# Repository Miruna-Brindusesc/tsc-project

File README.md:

# Proiect InkTime: Smartwatch nRF52840

## 1\. Diagrama Bloc

Diagrama de mai jos ilustreaza interconexiunile dintre unitatea centrala (MCU) si perifericele sistemului.

## 2\. Descriere Hardware

Ceasul este construit in jurul lui **nRF52840**, ales special pentru ca e foarte eficient si are Bluetooth inclus. Ideea de baza: consumam curent doar cand e absolut necesar.

### 2.1. Creierul (MCU)
* **nRF52840:** Un cip puternic care stie si Bluetooth 5.0 si USB. Are doua cristale de cuart pentru precizie maxima la masurarea timpului.
* **Antena:** Semnalul pleaca spre o antena ceramica. Ca sa avem semnal bun, am decupat planul de cupru de sub ea (zona de "keep-out").

### 2.2. Power & Battery
* **incarcare (BQ25180):** Se ocupa de alimentarea bateriei LiPo prin USB-C. il controlam prin **I2C** ca sa stim cand s-a incarcat.
* **Fuel Gauge (MAX17048):** E senzorul. Ne spune exact cat % mai are bateria, cu o eroare de sub 1%.
* **Regulator (RT6160A):** Transforma tensiunea variabila a bateriei intr-un **3.3V stabil** pentru toate componentele.
* **Protectie ESD:** Langa mufa USB-C am pus un cip minuscul (USBLC6) care atenueaza socurile de electricitate statica sa nu prajim placa.

### 2.3. Ecran si Vibratii
* **E-Paper Display:** Cel mai mare avantaj. Consuma curent **doar cand schimba imaginea**. Daca ceasul sta pe loc, consumul e zero.
* **Driverul de ecran:** Pentru ca ecranul are nevoie de tensiuni mari ca sa miste cerneala electronica, am adaugat un circuit special cu diode si condensatori de 50V.
* **Vibratii (Haptic):** Folosim un driver **DRV2605** care misca motorasul. E mult mai destept decat un simplu tranzistor, oferind vibratii mai fine.

### 2.4. Senzori si Butoane
* **Miscare (BMA423):** Accelerometrul care numara pasii. L-am legat pe **I2C** si are pini de intrerupere (INT) ca sa „trezeasca” ceasul cand ridici mana.
* **Butoane:** Avem 3 butoane cu filtre hardware (rezistente si condensatori) ca sa nu avem probleme cu „apasarile false” (debounce).

## 3\. Asociere pini

| Grupa de pini | Pini folositi | Componenta | Justificarea alegerii / Functia |
| :--- | :--- | :--- | :--- |
| **I2C (SDA/SCL)** | **P0.26 / P0.27** | BQ25180, MAX17048, BMA423, DRV2605 | Magistrala comuna; pinii au fost pozitionati departe de zona antenei pentru a evita interferentele RF. |
| **Display (SPI)** | **P0.13, P0.14, P0.19** | E-Paper Connector | Rutare scurta si directa catre conectorul FPC, minimizand lungimea traseelor de mare viteza. |
| **Display Control** | **P0.20, P0.21, P0.23** | E-Paper Connector | Pini GPIO pentru semnalele de DC, Reset si Busy. Pinul Busy actioneaza ca intrerupere (INT). |
| **Power Gate** | **P0.24** | Tranzistor Q1 (Load Switch) | Ofera curent suficient pentru a comuta poarta MOSFET-ului, oprind complet ecranul in standby. |
| **Butoane & Alerte**| **P1.00 - P1.06** | Butoane externe, Alerte IMU / Baterie | Folosirea exclusiva a Portului 1 pentru semnale lente/intreruperi, izolandu-le de magistralele de date si permitand functia de Wake-Up eficient. |
| **Haptic Enable** | **P0.25** | DRV2605 (Motor Haptic) | Pin GPIO folosit pentru pornirea/oprirea cipului haptic. |
| **USB** | **VBUS, D+, D-** | Conector USB-C | Pini hardware dedicati ai PHY-ului intern nRF52840 pentru comunicatie nativa. |
| **Programare (SWD)** | **SWDIO, SWDCLK, SWO**| Conector Tag-Connect | Pini dedicati din fabrica pentru interfata Serial Wire Debug. |
| **Ceas (Oscilator)** | **P0.00, P0.01** | Cristal 32.768 kHz | Pini hardware dedicati (LFXO) pentru conectarea cristalului extern necesar functiilor de Low-Power Sleep. |

## 4\. BOM
| Qty | Componenta | Designator | Cod JLC / Sursa | Datasheet / Link |
| :--- | :--- | :--- | :--- | :--- |
| 1 | **nRF52840 (MCU)** | U1 | [C190740](https://www.google.com/search?q=https://jlcpcb.com/partdetail/NordicSemicon-NRF52840_QIAA/C190740) | [Datasheet](https://www.google.com/search?q=https://infocenter.nordicsemi.com/pdf/nRF52840_PS_v1.1.pdf) |
| 1 | **BMA423 (IMU)** | IC3 | [C262-BMA423](https://jlcpcb.com/parts) | [Datasheet](https://www.google.com/search?q=https://www.bosch-sensortec.com/media/boschsensortec/downloads/datasheets/bst-bma423-ds000.pdf) |
| 1 | **BQ25180 (Charger)** | IC1 | [C595-BQ25180](https://jlcpcb.com/parts) | [Datasheet](https://www.ti.com/lit/ds/symlink/bq25180.pdf) |
| 1 | **MAX17048 (Fuel Gauge)** | U3 | [C329239](https://jlcpcb.com/parts) | [Datasheet](https://www.google.com/search?q=https://datasheets.maximintegrated.com/en/ds/MAX17048-MAX17049.pdf) |
| 1 | **RT6160A (DC/DC)** | IC9 | [C835-RT6160](https://jlcpcb.com/parts) | [Datasheet](https://www.google.com/search?q=https://www.richtek.com/assets/product_pdf/RT6160A/DS6160A-02.pdf) |
| 1 | **DRV2605 (Haptic)** | IC4 | [C519213](https://jlcpcb.com/parts) | [Datasheet](https://www.ti.com/lit/ds/symlink/drv2605.pdf) |
| 1 | **E-Paper Conn (24 pin)**| J1 | [C262444](https://jlcpcb.com/parts) | [Link Molex](https://www.molex.com/en-us/products/part-detail/5034802400) |
| 1 | **USB-C (16 pin)** | J4 | [C719112](https://jlcpcb.com/parts) | [Datasheet](https://www.google.com/search?q=https://datasheet.lcsc.com/lcsc/2110271930_KINGHELM-KH-TYPE-C-16P_C2835407.pdf) |
| 1 | **Antena 2.45GHz** | ANT1 | [C96280](https://jlcpcb.com/parts) | [Datasheet](https://www.johansontechnology.com/datasheets/2450AT18B100.pdf) |
| 3 | **Butoane EVP-AKE31A** | SW1-SW3 | [C519154](https://jlcpcb.com/parts) | [Datasheet](https://www.google.com/search?q=https://industrial.panasonic.com/cdbs/www-data/pdf/SMG0000/SMG0000C191.pdf) |
| 1 | **USBLC6-2 (ESD)** | D3 | [C75248](https://jlcpcb.com/parts) | [Datasheet](https://www.st.com/resource/en/datasheet/usblc6-2.pdf) |
| 1 | **DMG2305UX (P-FET)** | Q1 | [C14388](https://jlcpcb.com/parts) | [Datasheet](https://www.diodes.com/assets/Datasheets/DMG2305UX.pdf) |

## 5\. Decizii

### 5.1. Decizii de amplasare a componentelor

Privind asezarea componentelor pe PCB, au fost luate urmatoarele decizii strategice pentru a optimiza spatiul si performanta:

* **Planuri de Masa (GND Pours) pe ambele straturi:** Am implementat poligoane de GND atat pe stratul Top, cat si pe Bottom, cusute cu via-uri (vias). Aceasta decizie are trei roluri majore:
    1.  **Ecranare EMI:** Reduce zgomotul electric dintre traseele de semnal.
    2.  **Disipare Termica:** Ajuta la disiparea caldurii generate de convertorul DC/DC si de circuitul de incarcare a bateriei.
    3.  **Referinta RF:** Ofera un plan de referinta solid pentru performanta optima a antenei Bluetooth.
* **Amplasarea Antenei (RF Keep-out Zone):** Antena ceramica de 2.4GHz a fost plasata pe extrema dreapta a placii.

* **Gruparea Circuitului E-Paper:** Componentele voluminoase si zgomotoase aferente display-ului (bobina, diodele si condensatorii pentru tensiunile de VGH/VGL) sunt grupate extrem de compact in stanga, imediat langa conectorul FPC. Aceasta mentine traseele de inalta tensiune scurte si departe de liniile sensibile ale MCU-ului.

### 5.2. Erori

#### Erori ERC (Electrical Rule Check)
* **Conflicte de alimentare (U1, U3):** Softul da eroare pentru ca mai multi pini `VDD` se leaga la aceeasi retea (`3V3` sau `VBAT`). Conexiunile sunt 100% corecte conform datasheet-urilor; eroarea apare doar pentru ca softul e prea strict cu regulile de „Power Source”.
* **Pinii de decuplare (DEC1, DEC4):** Aceeasi poveste la nRF52840. Pinii sunt legati corect la condensatori externi exact cum cere producatorul, dar softul nu ii recunoaste ca noduri clasice de alimentare.
* **Componente fara valoare (SJ1):** Jumper-ul de pe placa (SJ1) este doar un bridge fizic (Solder Jumper) folosit pentru configurare. Fiind un simplu contact de fludor, e normal sa nu aiba o valoare numerica (gen 10kΩ).
* **Erorile de tip "Only one pin on net"** (pe SDA/SCL) arata ca acele trasee sunt lasate libere.

#### Erori DRC (Design Rule Check)
Deoarece acest PCB este un *Proof of Concept* software si nu merge fizic la o fabrica, am prioritizat logica si functionalitatea in fata unui raport DRC complet verde:
* **Erori de margine (Board Outline Clearance):** Sunt 8 erori aici.Conectorul USB-C si butoanele sunt apropiate de marginile placutei, ceea ce declanseaza automat eroarea.
* **Suprapuneri pe planul de masa (Polygon Overlap):** Placa foloseste piese minuscule (0201/0402) si este foarte aglomerata. Am fortat poligonul de masa (GND) sa acopere cat mai mult spatiu pentru o buna disipare termica. Asta a generat niste erori de "clearance" la pad-uri, dar am preferat un plan de masa solid in detrimentul unui DRC perfect.

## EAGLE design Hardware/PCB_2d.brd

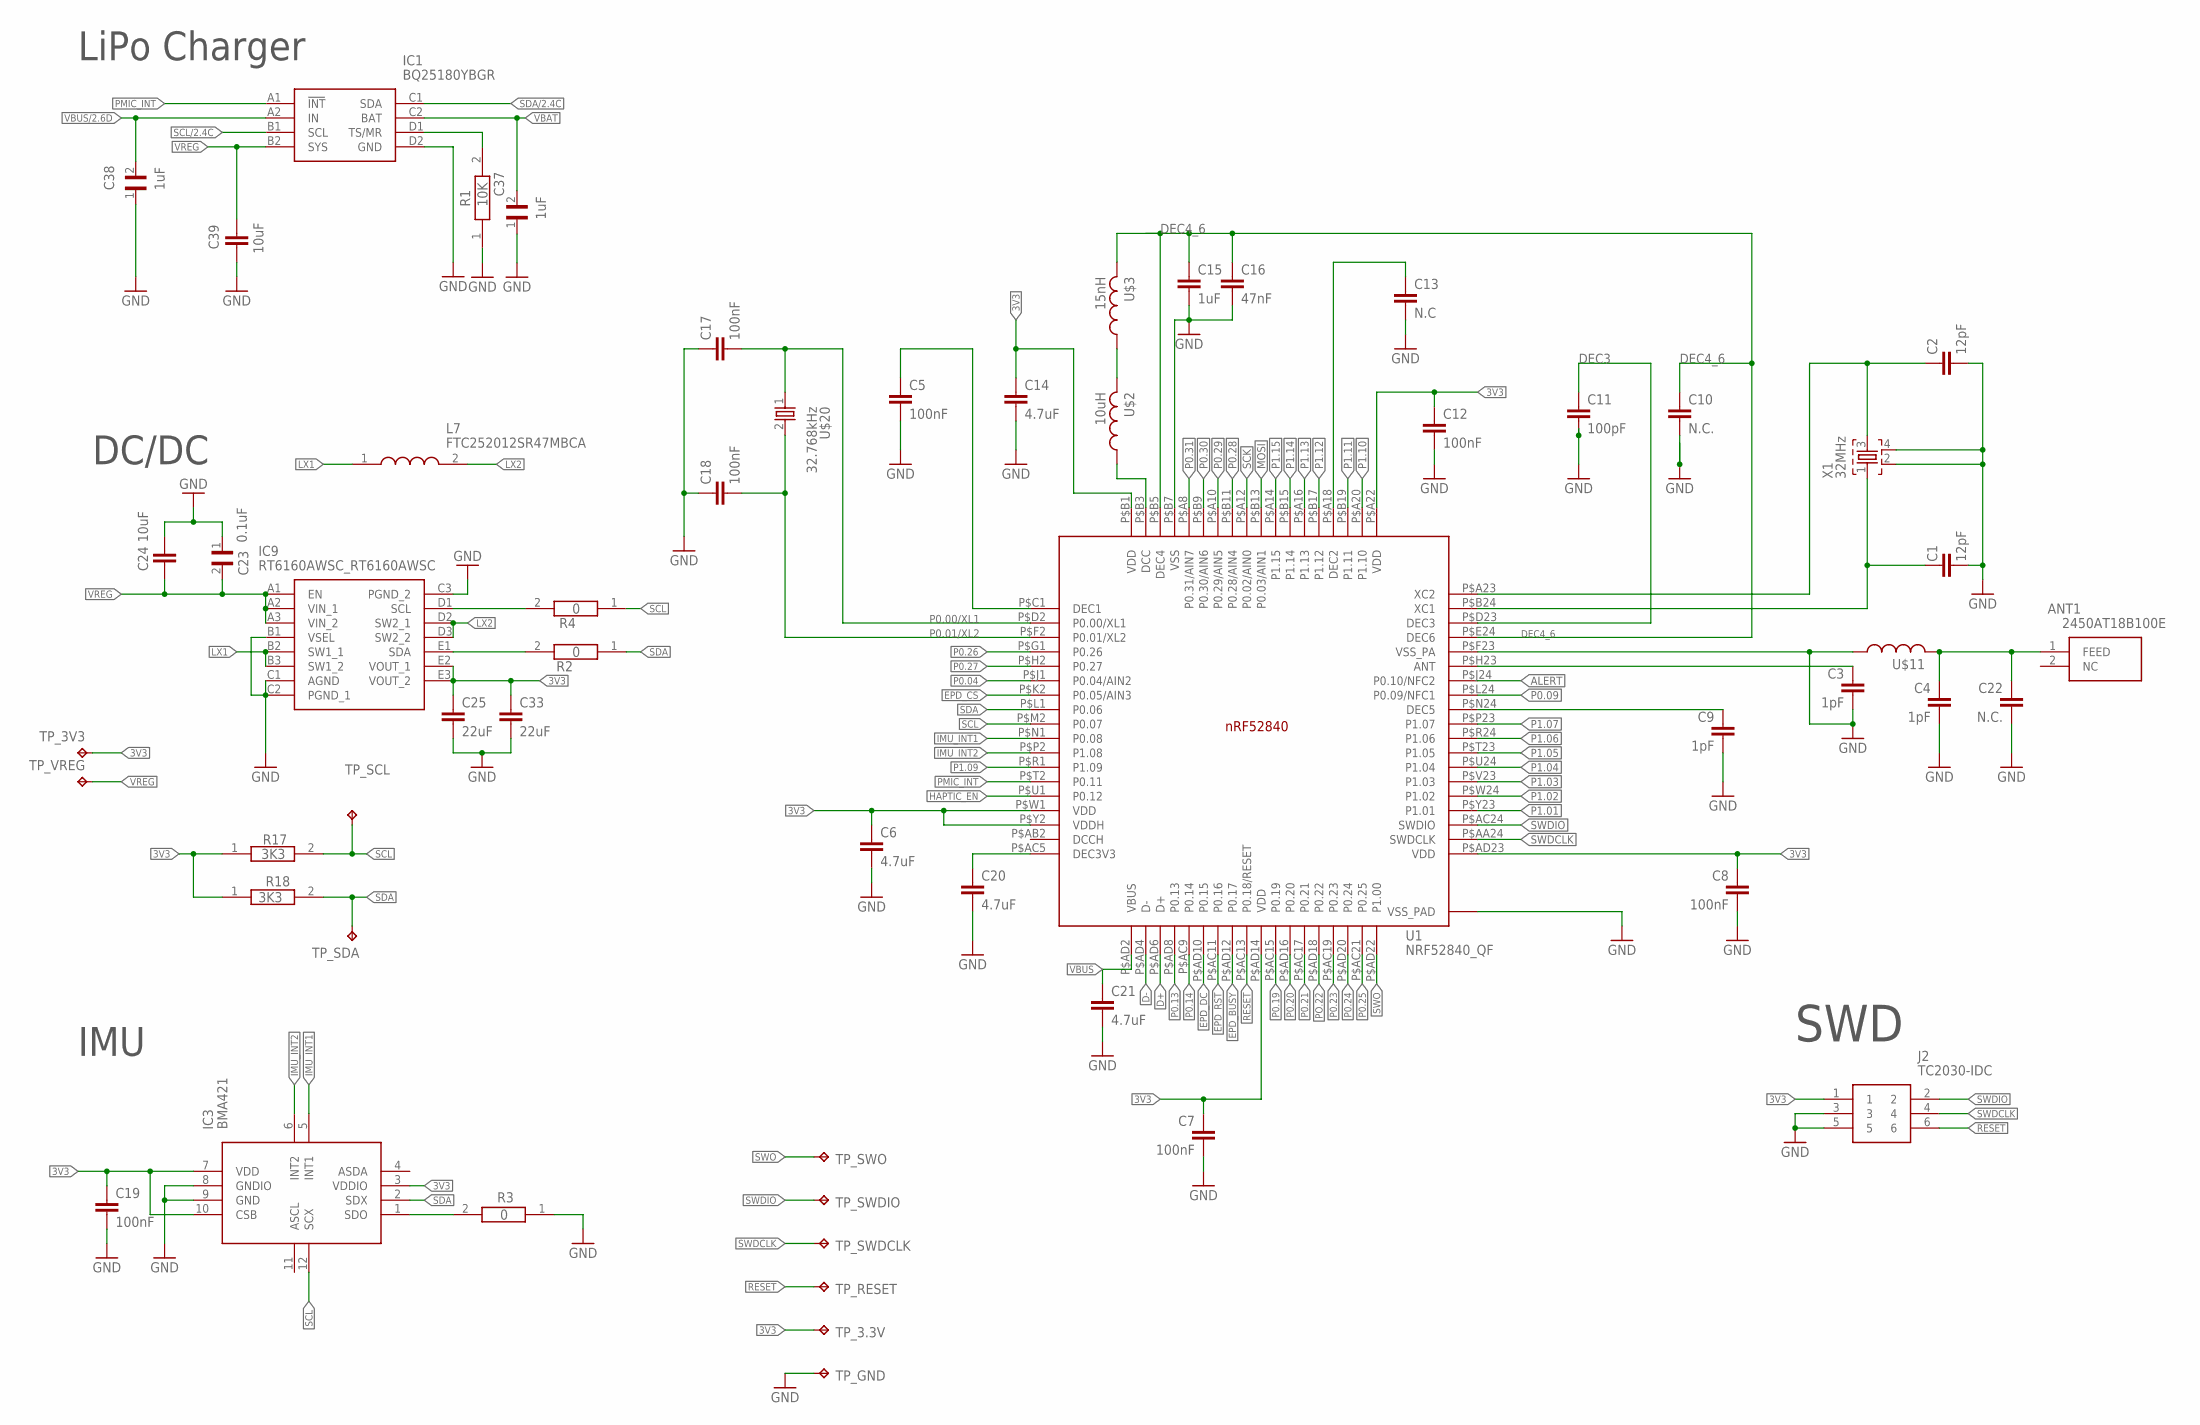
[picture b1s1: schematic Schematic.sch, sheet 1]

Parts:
ANT1: 2450AT18B100E; 2450AT18B100E_ANTC3216X140N
C1, C2: 12pF; NORDIC_NRF_3_RESC0201_L
C3, C4, C9: 1pF; NORDIC_NRF_3_RESC0201_L
C5, C7, C8, C12, C17, C18, C19: 100nF; NORDIC_NRF_3_RESC0201_L
C6, C14, C20, C21: 4.7uF; PERFECT_0402_0402
C10, C22: N.C.; NORDIC_NRF_3_RESC0201_L
C11: 100pF; NORDIC_NRF_3_RESC0201_L
C13: N.C; NORDIC_NRF_3_RESC0201_L
C15: 1uF; PERFECT_0402_0402
C16: 47nF; NORDIC_NRF_3_RESC0201_L
C23: 0.1uF; GRM011R60J152KE01L_2_CAPC0201X13N
C24, C39: 10uF; PERFECT_0402_0402
C25, C33: 22uF; PERFECT_0402_0402
C37, C38: 1uF; GRM011R60J152KE01L_1_0201
IC1: BQ25180YBGR; BQ25180YBGR_BGA8C40P2X4_100X155X50
IC3: BMA421; BMA423_BMA423
IC9: RT6160AWSC_RT6160AWSC; RT6160AWSC_BGA15C40P3X5_140X230X60
J2: TC2030-IDC; TC2030-IDC_TC2030IDC
L7: FTC252012SR47MBCA; MLP2016SR47MT0S1_INDC2016X100N
R1: 10K; CPF0201D7K68C1_0201
R2, R3, R4: 0; CPF0201D7K68C1_0201
R17, R18: 3K3; CPF0201D7K68C1_0201
TP_3.3V, TP_3V3: HECTOR_WATCH_1_TPTP20R; HECTOR_WATCH_1_TP20R
TP_GND: HECTOR_WATCH_1_TPTP20R; HECTOR_WATCH_1_TP20R
TP_RESET: HECTOR_WATCH_1_TPTP20R; HECTOR_WATCH_1_TP20R
TP_SCL: HECTOR_WATCH_1_TPTP20R; HECTOR_WATCH_1_TP20R
TP_SDA: HECTOR_WATCH_1_TPTP20R; HECTOR_WATCH_1_TP20R
TP_SWDCLK: HECTOR_WATCH_1_TPTP20R; HECTOR_WATCH_1_TP20R
TP_SWDIO: HECTOR_WATCH_1_TPTP20R; HECTOR_WATCH_1_TP20R
TP_SWO: HECTOR_WATCH_1_TPTP20R; HECTOR_WATCH_1_TP20R
TP_VREG: HECTOR_WATCH_1_TPTP20R; HECTOR_WATCH_1_TP20R
U1: NRF52840_QF; NORDIC_NRF_4_AQFN50P700X700X85_HS-74N
U$2: 10uH; NORDIC_NRF_2_RESC0402_L
U$3: 15nH; NORDIC_NRF_2_RESC0402_L
U$11: NORDIC_NRF_2_INDUCTOR_0402_L; NORDIC_NRF_2_RESC0402_L
U$20: 32.768kHz; NORDIC_NRF_1_XTAL_3215_N
X1: 32MHz; NORDIC_NRF_BT-XTAL_2016_N

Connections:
3V3: C6.1, C7.1, C8.1, C12.1, C14.1, C19.1, C25.1, C33.1, IC3.3 (VDDIO), IC3.7 (VDD), IC3.10 (CSB), IC9.E2 (VOUT_1), IC9.E3 (VOUT_2), J2.1, R17.1, R18.1, TP_3.3V.TP, TP_3V3.TP, U1.P$A22 (VDD), U1.P$AD14 (VDD), U1.P$AD23 (VDD), U1.P$B1 (VDD), U1.P$W1 (VDD), U1.P$Y2 (VDDH); also elsewhere on the board
ALERT: U1.P$J24 (P0.10/NFC2); also elsewhere on the board
D+: U1.P$AD6 (D+); also elsewhere on the board
D-: U1.P$AD4 (D-); also elsewhere on the board
DEC3: C11.1, U1.P$D23 (DEC3)
DEC4_6: C10.1, C15.1, C16.1, U1.P$B5 (DEC4), U1.P$E24 (DEC6), U$3.2
EPD_BUSY: U1.P$AD12 (P0.17); also elsewhere on the board
EPD_CS: U1.P$K2 (P0.05/AIN3); also elsewhere on the board
EPD_DC: U1.P$AD10 (P0.15); also elsewhere on the board
EPD_RST: U1.P$AC11 (P0.16); also elsewhere on the board
GND: C1.2, C2.2, C3.2, C4.2, C5.2, C6.2, C7.2, C8.2, C9.2, C10.2, C11.2, C12.2, C13.2, C14.2, C15.2, C16.2, C17.1, C18.1, C19.2, C20.2, C21.2, C22.2, C23.1, C24.1, C25.2, C33.2, C37.1, C38.1, C39.2, IC1.D2 (GND), IC3.8 (GNDIO), IC3.9 (GND), IC9.B1 (VSEL), IC9.C1 (AGND), IC9.C2 (PGND_1), IC9.C3 (PGND_2), J2.3, J2.5, R1.1, R3.1, TP_GND.TP, U1.P$74 (VSS_PAD), U1.P$75 (VSS_PAD), U1.P$76 (VSS_PAD), U1.P$77 (VSS_PAD), U1.P$78 (VSS_PAD), U1.P$79 (VSS_PAD), U1.P$80 (VSS_PAD), U1.P$81 (VSS_PAD), U1.P$82 (VSS_PAD), U1.P$83 (VSS_PAD), U1.P$84 (VSS_PAD), U1.P$85 (VSS_PAD), U1.P$86 (VSS_PAD), U1.P$87 (VSS_PAD), U1.P$88 (VSS_PAD), U1.P$89 (VSS_PAD), U1.P$90 (VSS_PAD), U1.P$B7 (VSS), U1.P$F23 (VSS_PA), U$11.1, X1.2, X1.4; also elsewhere on the board
HAPTIC_EN: U1.P$U1 (P0.12); also elsewhere on the board
IMU_INT1: IC3.5 (INT1), U1.P$N1 (P0.08)
IMU_INT2: IC3.6 (INT2), U1.P$P2 (P1.08)
LX1: IC9.B2 (SW1_1), IC9.B3 (SW1_2), L7.1
LX2: IC9.D2 (SW2_1), IC9.D3 (SW2_2), L7.2
MOSI: U1.P$B13 (P0.03/AIN1); also elsewhere on the board
unnamed: U1.P$B3 (DCC), U$2.1
unnamed: U$2.2, U$3.1
unnamed: C13.1, U1.P$A18 (DEC2)
unnamed: IC9.E1 (SDA), R2.2
unnamed: IC9.D1 (SCL), R4.2
unnamed: C1.1, U1.P$B24 (XC1), X1.1
unnamed: C2.1, U1.P$A23 (XC2), X1.3
unnamed: ANT1.1 (FEED), C4.1, C22.1, U$11.2
unnamed: C3.1, U1.P$H23 (ANT)
unnamed: C9.1, U1.P$N24 (DEC5)
unnamed: C5.1, U1.P$C1 (DEC1)
unnamed: C20.1, U1.P$AC5 (DEC3V3)
unnamed: IC1.D1 (TS/MR), R1.2
unnamed: IC3.1 (SDO), R3.2
P0.00/XL1: C17.2, U1.P$D2 (P0.00/XL1), U$20.1
P0.01/XL2: C18.2, U1.P$F2 (P0.01/XL2), U$20.2
P0.04: U1.P$J1 (P0.04/AIN2)
P0.09: U1.P$L24 (P0.09/NFC1)
P0.13: U1.P$AD8 (P0.13); also elsewhere on the board
P0.14: U1.P$AC9 (P0.14); also elsewhere on the board
P0.19: U1.P$AC15 (P0.19)
P0.20: U1.P$AD16 (P0.20)
P0.21: U1.P$AC17 (P0.21)
P0.23: U1.P$AC19 (P0.23)
P0.24: U1.P$AD20 (P0.24)
P0.25: U1.P$AC21 (P0.25)
P0.26: U1.P$G1 (P0.26)
P0.27: U1.P$H2 (P0.27)
P0.28: U1.P$B11 (P0.28/AIN4)
P0.29: U1.P$A10 (P0.29/AIN5)
P0.30: U1.P$B9 (P0.30/AIN6)
P0.31: U1.P$A8 (P0.31/AIN7)
P1.01: U1.P$Y23 (P1.01); also elsewhere on the board
P1.02: U1.P$W24 (P1.02); also elsewhere on the board
P1.03: U1.P$V23 (P1.03)
P1.04: U1.P$U24 (P1.04)
P1.05: U1.P$T23 (P1.05)
P1.06: U1.P$R24 (P1.06)
P1.07: U1.P$P23 (P1.07)
P1.09: U1.P$R1 (P1.09)
P1.10: U1.P$A20 (P1.10)
P1.11: U1.P$B19 (P1.11)
P1.12: U1.P$B17 (P1.12)
P1.13: U1.P$A16 (P1.13)
P1.14: U1.P$B15 (P1.14)
P1.15: U1.P$A14 (P1.15)
PMIC_INT: IC1.A1 (!INT), U1.P$T2 (P0.11)
PO.22: U1.P$AD18 (P0.22)
RESET: J2.6, TP_RESET.TP, U1.P$AC13 (P0.18/RESET)
SCK: U1.P$A12 (P0.02/AIN0); also elsewhere on the board
SCL: IC3.12 (SCX), R4.1, R17.2, TP_SCL.TP, U1.P$M2 (P0.07); also elsewhere on the board
SCL/2.4C: IC1.B1 (SCL)
SDA: IC3.2 (SDX), R2.1, R18.2, TP_SDA.TP, U1.P$L1 (P0.06); also elsewhere on the board
SDA/2.4C: IC1.C1 (SDA)
SWDCLK: J2.4, TP_SWDCLK.TP, U1.P$AA24 (SWDCLK)
SWDIO: J2.2, TP_SWDIO.TP, U1.P$AC24 (SWDIO)
SWO: TP_SWO.TP, U1.P$AD22 (P1.00)
VBAT: C37.2, IC1.C2 (BAT); also elsewhere on the board
VBUS: C21.1, U1.P$AD2 (VBUS); also elsewhere on the board
VBUS/2.6D: C38.2, IC1.A2 (IN)
VREG: C23.2, C24.2, C39.1, IC1.B2 (SYS), IC9.A1 (EN), IC9.A2 (VIN_1), IC9.A3 (VIN_2), TP_VREG.TP

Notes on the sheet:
DC/DC
LiPo Charger
IMU
SWD

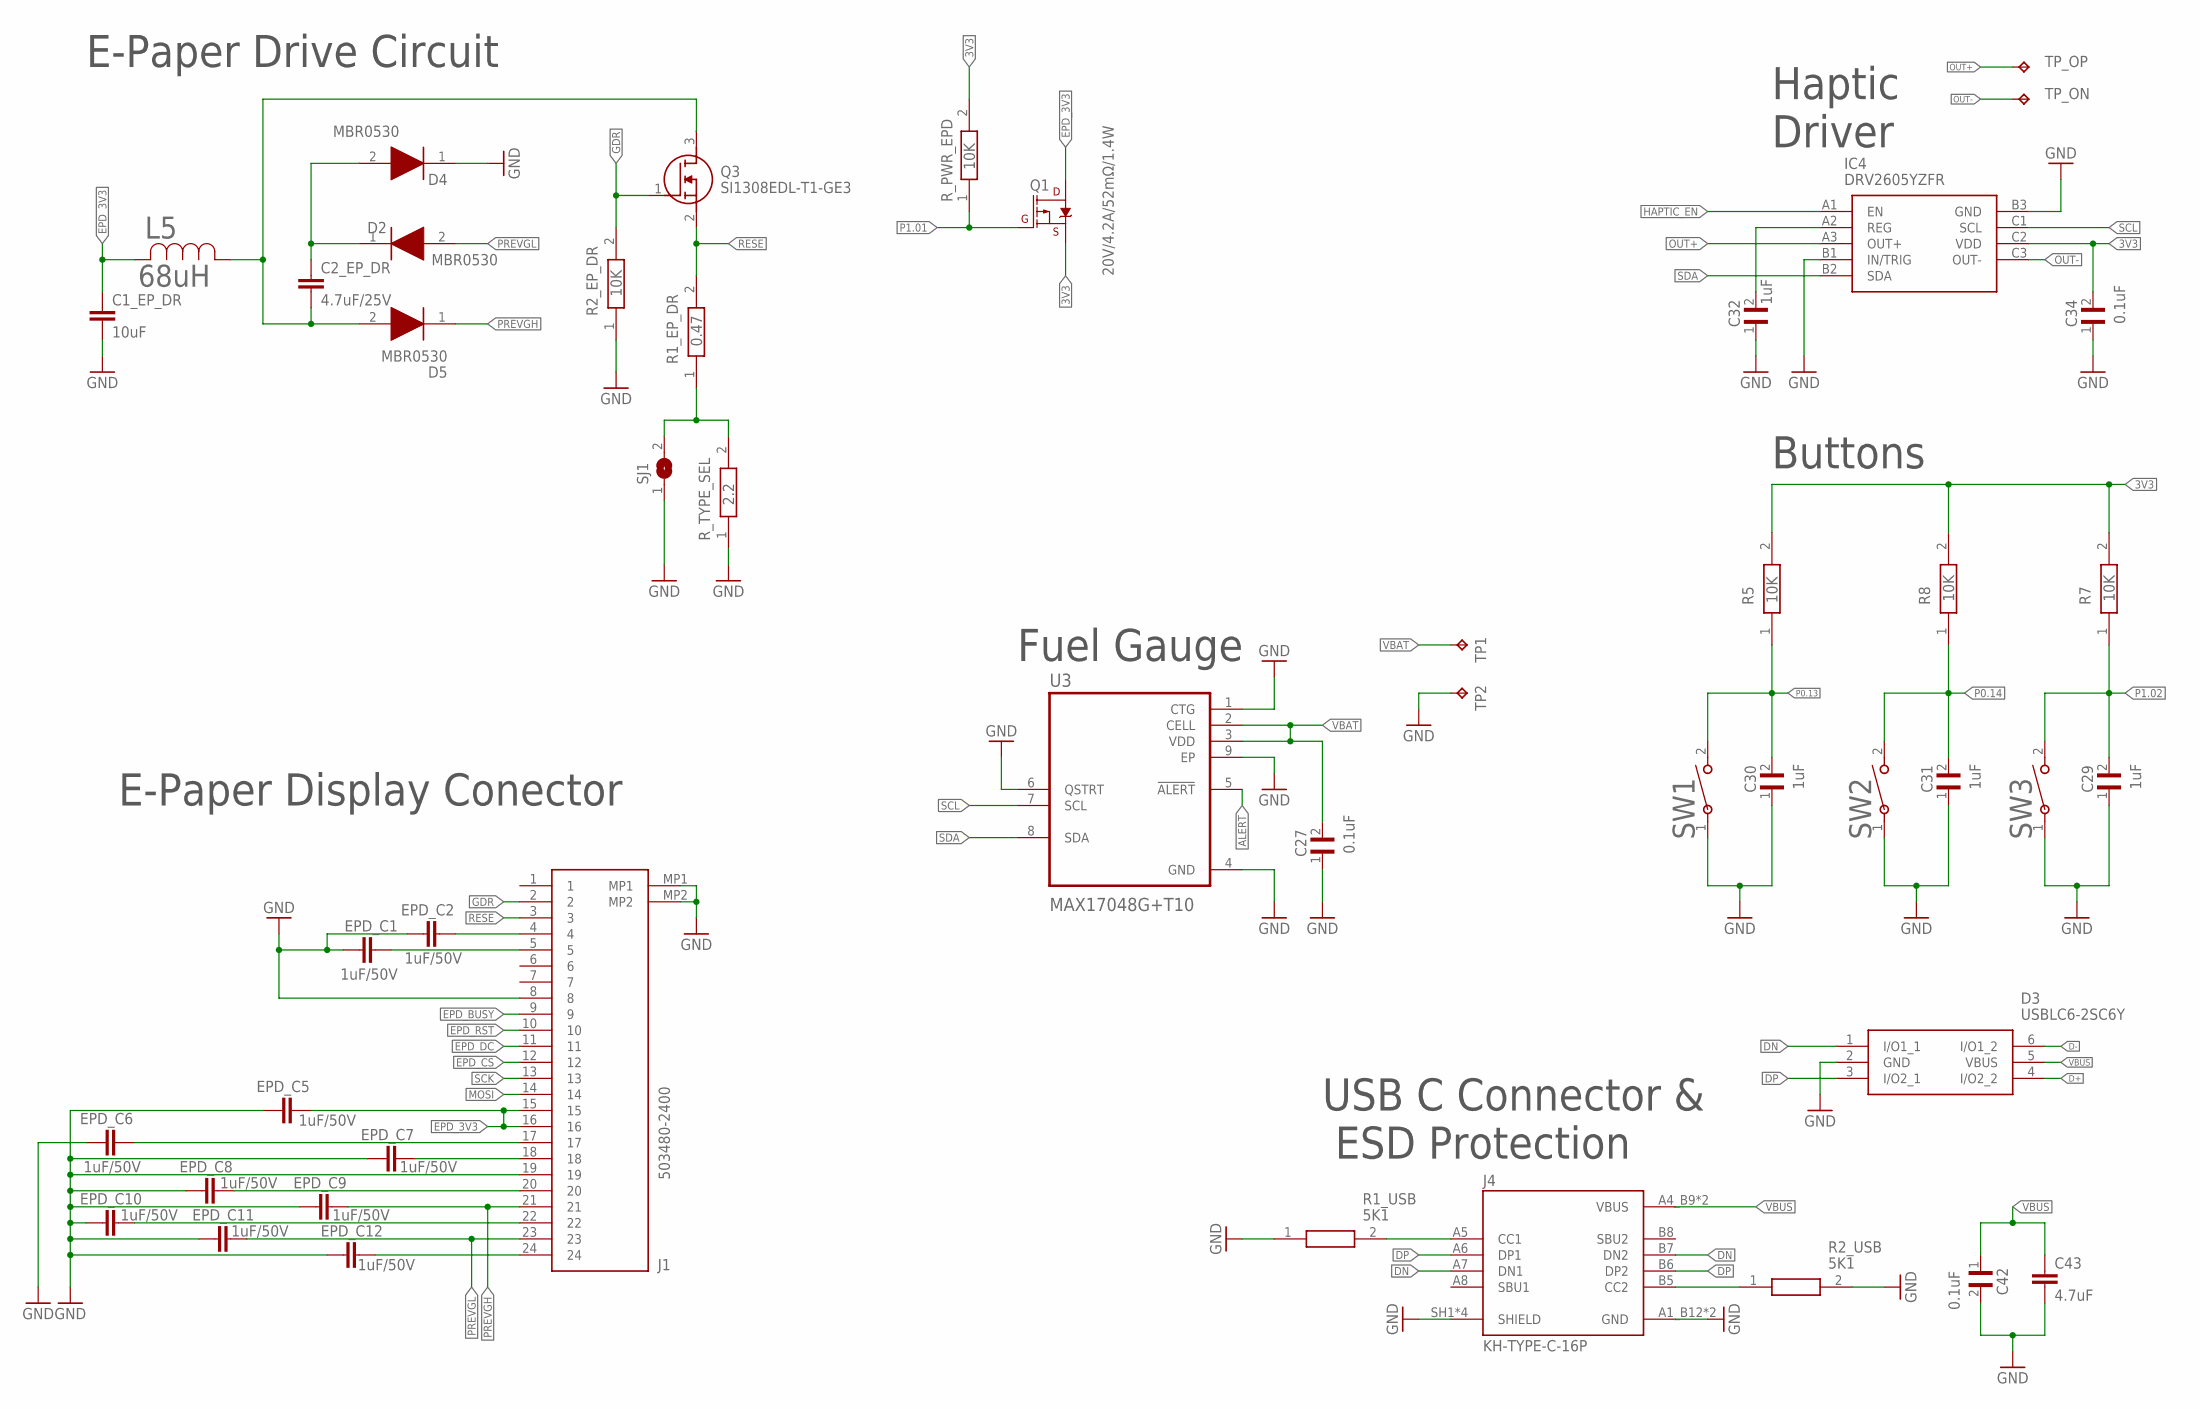
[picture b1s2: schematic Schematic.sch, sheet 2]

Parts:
C1_EP_DR: 10uF; PERFECT_0402_0402
C2_EP_DR: 4.7uF/25V; PERFECT_0402_0402
C27, C34, C42: 0.1uF; GRM011R60J152KE01L_2_CAPC0201X13N
C29, C30, C31, C32: 1uF; GRM011R60J152KE01L_2_CAPC0201X13N
C43: 4.7uF; PERFECT_0402_0402
D2, D4, D5: MBR0530; ESP32_C6_LIBRARY_5_SOD3716X135N
D3: USBLC6-2SC6Y; ESP32_C6_LIBRARY_3_SOT95P280X145-6N
EPD_C1, EPD_C2, EPD_C5, EPD_C6, EPD_C7, EPD_C8, EPD_C9, EPD_C10, EPD_C11, EPD_C12: 1uF/50V; PERFECT_0402_0402
IC4: DRV2605YZFR; DRV2605YZFR_BGA9C50P3X3_144X144X62
J1: 503480-2400; 503480-2400_5034802400
J4: KH-TYPE-C-16P; KH-TYPE-C-16P_KINGHELM_KH-TYPE-C-16P
L5: 68uH; ESP32_C6_LIBRARY_2_IND_4828-WE-TPC_WRE
Q1: 20V/4.2A/52mΩ/1.4W; ESP32_C6_LIBRARY_4_ESP32_C6_LIBRARY_4_ESP32_C6_LIBRARY_4_ES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
Q3: SI1308EDL-T1-GE3; ESP32_C6_LIBRARY_6_SOT65P210X110-3N
R1_EP_DR: 0.47; CPF0201D7K68C1_0201
R1_USB, R2_USB: 5K1; CPF0201D7K68C1_0201
R2_EP_DR, R5, R7, R8: 10K; CPF0201D7K68C1_0201
R_PWR_EPD: 10K; CPF0201D7K68C1_0201
R_TYPE_SEL: 2.2; CPF0201D7K68C1_0201
SJ1: ESP32_C6_LIBRARY_7_JUMPER_SJ
SW1, SW2, SW3: 2025-10-22_07-23-44_LIBRARY_EVP-AKE31ASW_EVP-AKE3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; 2025-10-22_07-23-44_LIBRARY_SW_EVP-AKE31A_PAN
TP1, TP2: HECTOR_WATCH_1_TPTP20R; HECTOR_WATCH_1_TP20R
TP_ON: HECTOR_WATCH_1_TPTP20R; HECTOR_WATCH_1_TP20R
TP_OP: HECTOR_WATCH_1_TPTP20R; HECTOR_WATCH_1_TP20R
U3: MAX17048G+T10; ESP32_C6_LIBRARY_SON50P200X200X80-9N

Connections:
3V3: C34.2, IC4.C2 (VDD), Q1.2 (S), R5.2, R7.2, R8.2, R_PWR_EPD.2; also elsewhere on the board
ALERT: U3.5 (!ALERT); also elsewhere on the board
D+: D3.4 (I/O2_2); also elsewhere on the board
D-: D3.6 (I/O1_2); also elsewhere on the board
DN: D3.1 (I/O1_1), J4.A7 (DN1), J4.B7 (DN2)
DP: D3.3 (I/O2_1), J4.A6 (DP1), J4.B6 (DP2)
EPD_3V3: C1_EP_DR.1, EPD_C5.2, J1.15, J1.16, L5.2, Q1.3 (D)
EPD_BUSY: J1.9; also elsewhere on the board
EPD_CS: J1.12; also elsewhere on the board
EPD_DC: J1.11; also elsewhere on the board
EPD_RST: J1.10; also elsewhere on the board
GDR: J1.2, Q3.1 (G), R2_EP_DR.2
GND: C1_EP_DR.2, C27.1, C29.1, C30.1, C31.1, C32.1, C34.1, C42.2, C43.2, D3.2 (GND), D4.1 (K), EPD_C1.1, EPD_C2.1, EPD_C5.1, EPD_C6.1, EPD_C7.1, EPD_C8.1, EPD_C9.1, EPD_C10.1, EPD_C11.1, EPD_C12.1, IC4.B1 (IN/TRIG), IC4.B3 (GND), J1.8, J1.19, J1.MP1, J1.MP2, J4.A1_B12 (GND), J4.A12_B1 (GND), J4.SH1 (SHIELD), J4.SH2 (SHIELD), J4.SH3 (SHIELD), J4.SH4 (SHIELD), R1_USB.1, R2_EP_DR.1, R2_USB.2, R_TYPE_SEL.1, SJ1.1, SW1.1, SW2.1, SW3.1, TP2.TP, U3.1 (CTG), U3.4 (GND), U3.6 (QSTRT), U3.9 (EP); also elsewhere on the board
HAPTIC_EN: IC4.A1 (EN); also elsewhere on the board
MOSI: J1.14; also elsewhere on the board
unnamed: EPD_C2.2, J1.4
unnamed: C2_EP_DR.1, D2.1 (K), D4.2 (A)
unnamed: C2_EP_DR.2, D5.2 (A), L5.1, Q3.3 (D)
unnamed: R1_EP_DR.1, R_TYPE_SEL.2, SJ1.2
unnamed: EPD_C1.2, J1.5
unnamed: EPD_C6.2, J1.17
unnamed: EPD_C7.2, J1.18
unnamed: EPD_C8.2, J1.20
unnamed: J4.A5 (CC1), R1_USB.2
unnamed: EPD_C10.2, J1.22
unnamed: EPD_C12.2, J1.24
unnamed: J4.B5 (CC2), R2_USB.1
unnamed: C32.2, IC4.A2 (REG)
OUT+: IC4.A3 (OUT+), TP_OP.TP
OUT-: IC4.C3 (OUT-), TP_ON.TP
P0.13: C30.2, R5.1, SW1.2; also elsewhere on the board
P0.14: C31.2, R8.1, SW2.2; also elsewhere on the board
P1.01: Q1.1 (G), R_PWR_EPD.1; also elsewhere on the board
P1.02: C29.2, R7.1, SW3.2; also elsewhere on the board
PREVGH: D5.1 (K), EPD_C9.2, J1.21
PREVGL: D2.2 (A), EPD_C11.2, J1.23
RESE: J1.3, Q3.2 (S), R1_EP_DR.2
SCK: J1.13; also elsewhere on the board
SCL: IC4.C1 (SCL), U3.7 (SCL); also elsewhere on the board
SDA: IC4.B2 (SDA), U3.8 (SDA); also elsewhere on the board
VBAT: C27.2, TP1.TP, U3.2 (CELL), U3.3 (VDD); also elsewhere on the board
VBUS: C42.1, C43.1, D3.5 (VBUS), J4.A4_B9 (VBUS), J4.A9_B4 (VBUS); also elsewhere on the board

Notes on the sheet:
USB C Connector & ESD Protection
Buttons
Fuel Gauge
Haptic Driver
E-Paper Drive Circuit
E-Paper Display Conector

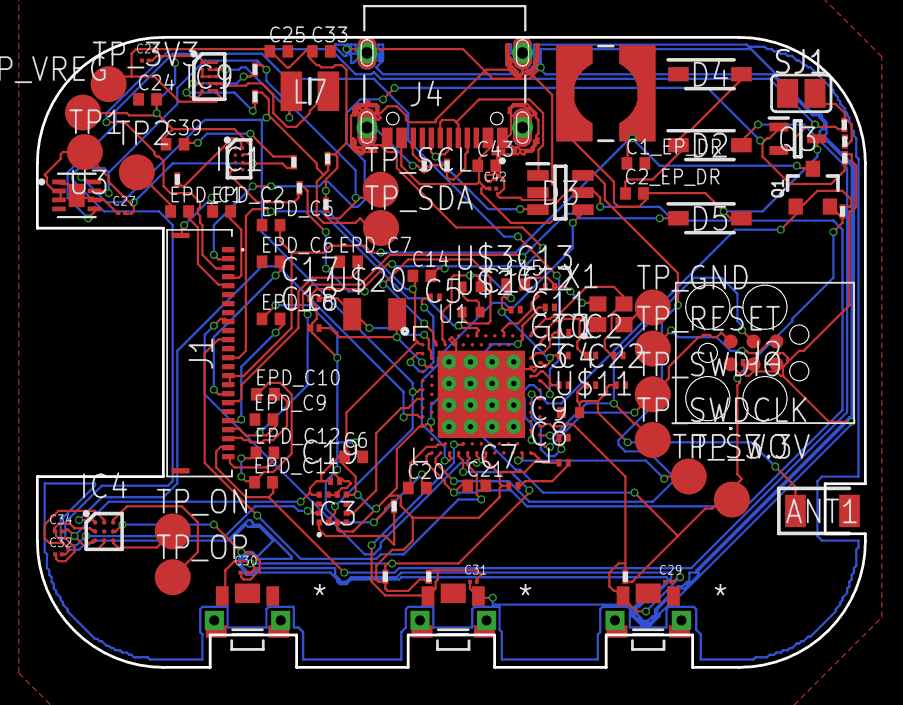
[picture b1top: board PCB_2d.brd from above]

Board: 2 copper layers, 46.0 x 35.0 mm, 105 parts (0 on the bottom side), 71 nets.

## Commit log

2026-04-10 Add directories and README
2026-04-10 Add Manufacturing files and Hardware files
2026-04-10 Add GNU General Public License v3
2026-04-10 Add Images files and Mechanical file
2026-04-20 Add modified files: Schematic, PCB_2d, PCB_3d in .f3d format(Fusion crashes at .step export), exploded_view in .f3z format(same problem), bill.bom, gerbers.zip, pick.cpl.
2026-04-20 Improve README
2026-04-20 Add diagram

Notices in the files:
parts and their libraries:
COPYRIGHT: Copyright (C) 2024 Ultra Librarian. All rights reserved.
COPYRIGHT: Copyright (C) 2025 Ultra Librarian. All rights reserved.
